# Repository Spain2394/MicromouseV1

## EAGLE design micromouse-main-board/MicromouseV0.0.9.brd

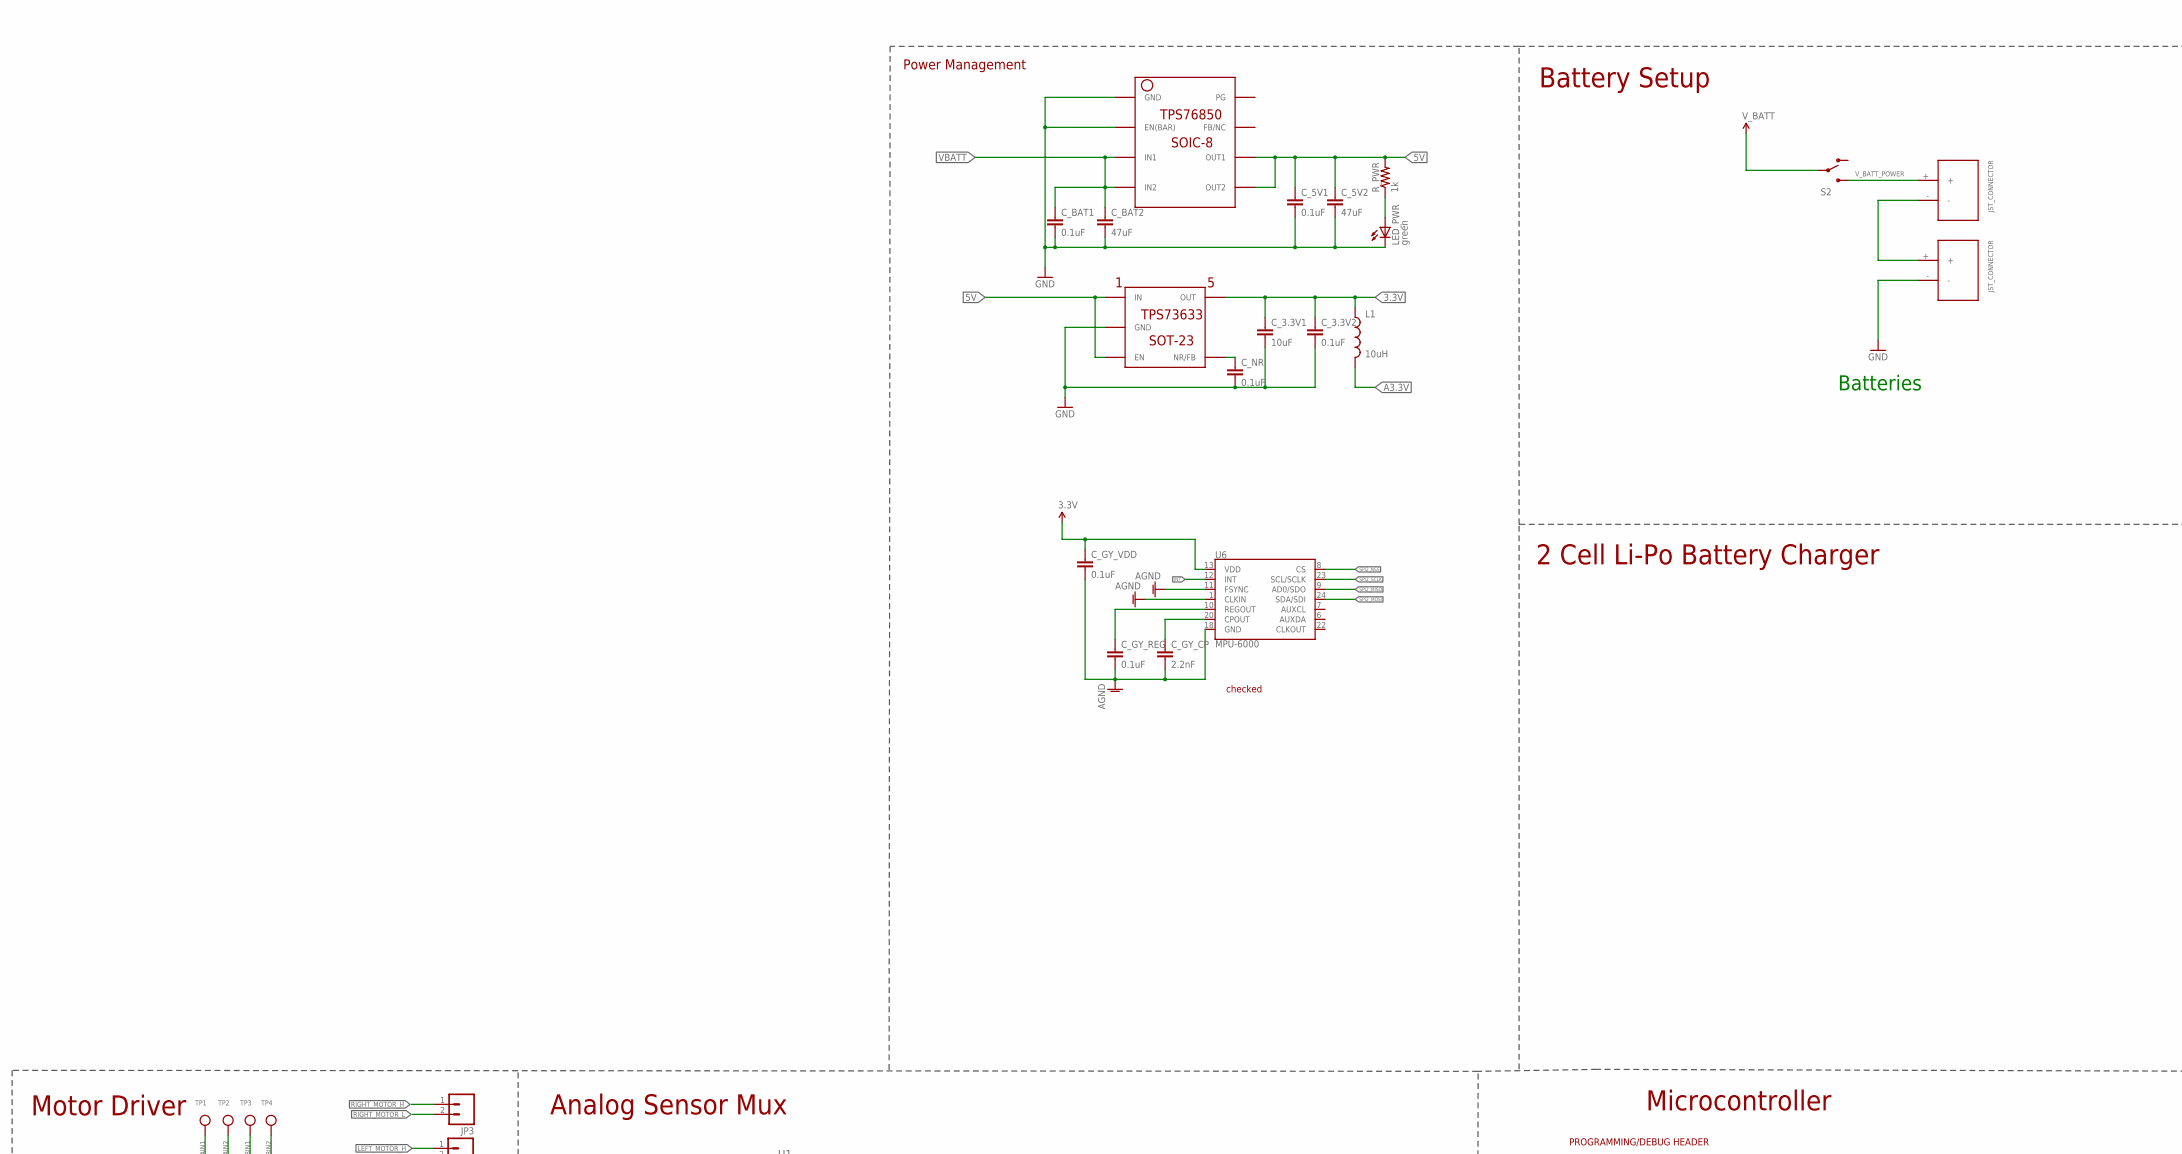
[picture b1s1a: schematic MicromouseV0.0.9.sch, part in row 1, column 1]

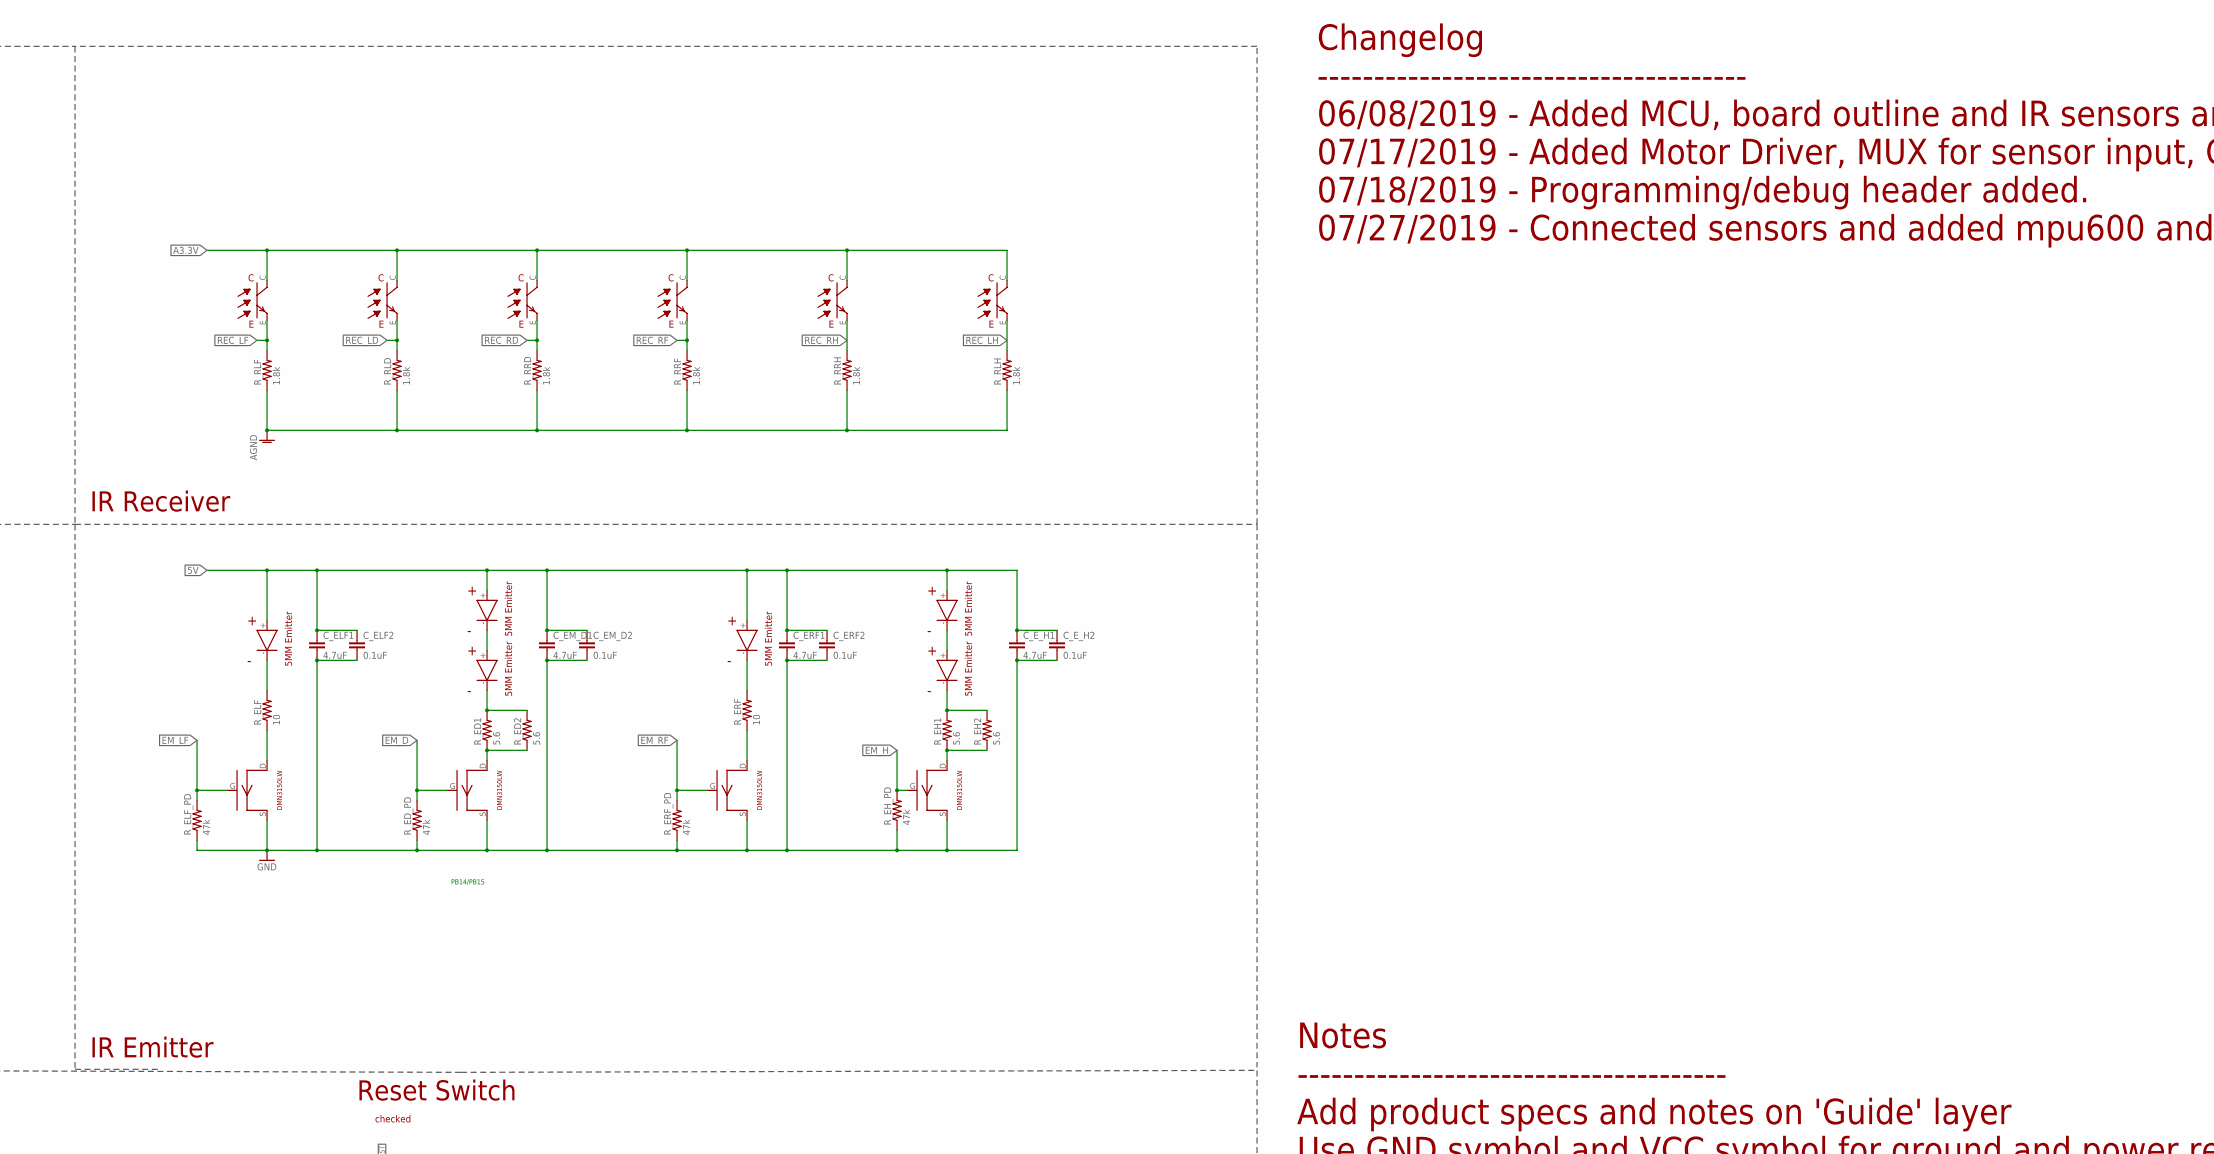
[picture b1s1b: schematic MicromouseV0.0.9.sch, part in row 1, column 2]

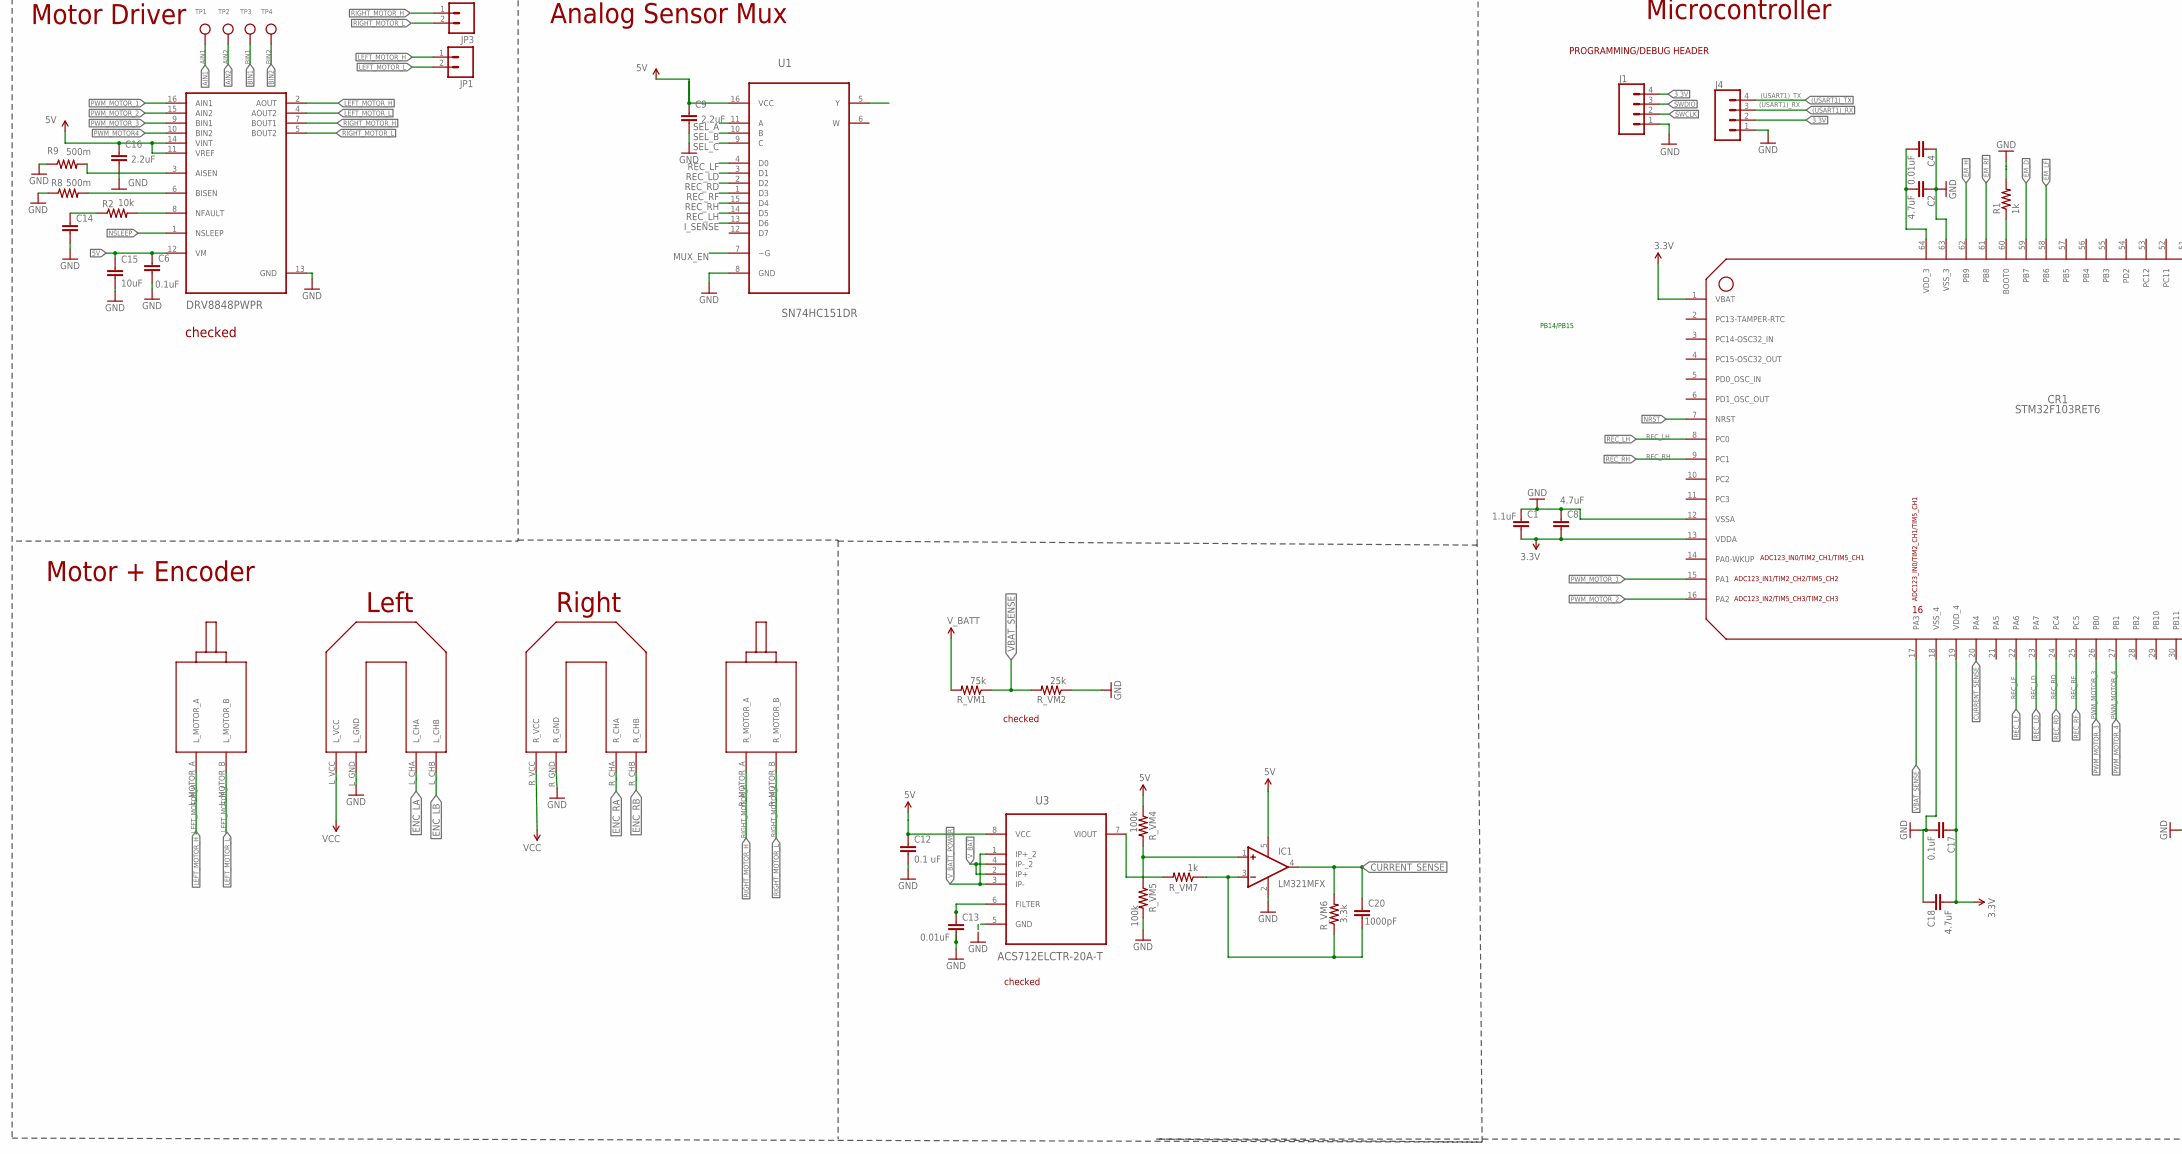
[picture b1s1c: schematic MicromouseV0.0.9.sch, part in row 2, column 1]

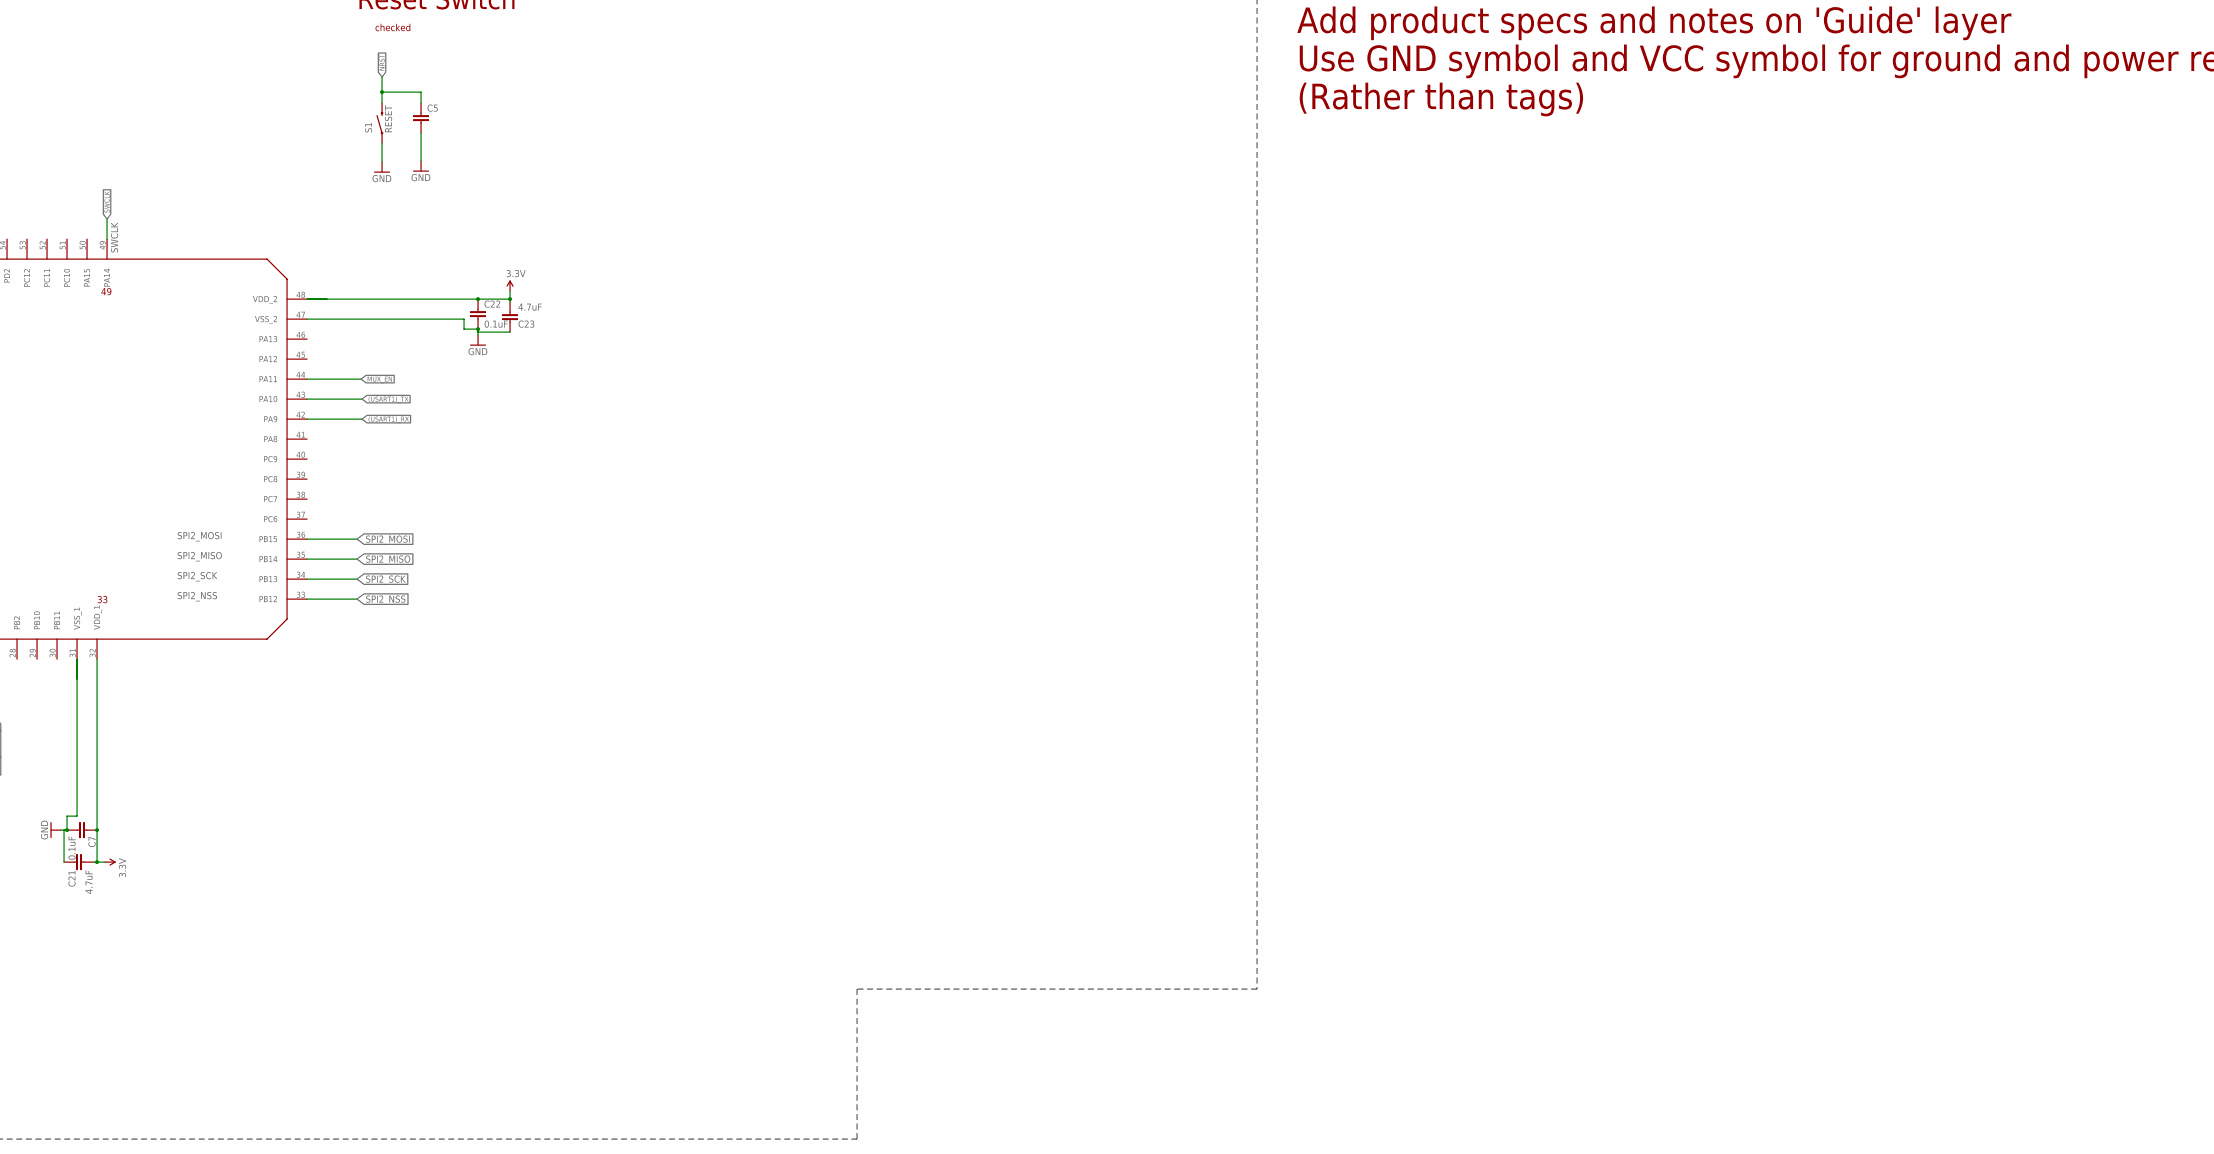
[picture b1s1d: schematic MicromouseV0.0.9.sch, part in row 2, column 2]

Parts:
C1: 1.1uF; 0603-CAP
C2, C8, C18, C21, C23: 4.7uF; 0603-CAP
C4, C13: 0.01uF; 0603-CAP
C5, C14: CAP0603-CAP; 0603-CAP
C6, C7, C17, C22: 0.1uF; 0603-CAP
C9, C16: 2.2uF; 0603-CAP
C12: 0.1 uF; 0603-CAP
C15: 10uF; 0603-CAP
C20: 1000pF; 0603-CAP
CR1: STM32F103RET6; LQFP-64
C_3.3V1: 10uF; 0603-CAP
C_3.3V2, C_5V1: 0.1uF; 0603-CAP
C_5V2: 47uF; 1210
C_BAT1: 0.1uF; 0603-CAP
C_BAT2: 47uF; 1210
C_ELF1: 4.7uF; 0603-CAP
C_ELF2: 0.1uF; 0603-CAP
C_EM_D1: 4.7uF; 0603-CAP
C_EM_D2: 0.1uF; 0603-CAP
C_ERF1: 4.7uF; 0603-CAP
C_ERF2: 0.1uF; 0603-CAP
C_E_H1: 4.7uF; 0603-CAP
C_E_H2: 0.1uF; 0603-CAP
C_GY_CP: 2.2nF; 0603-CAP
C_GY_REG: 0.1uF; 0603-CAP
C_GY_VDD: 0.1uF; 0603-CAP
C_NR: 0.1uF; 0603-CAP
IC1: LM321MFX; SOT23-5
J1, J4: CONN_04; 1X04
JP1, JP3: M02POLAR; MOLEX-1X2
L1: 10uH; 1007
LED_PWR: green; LED-1206
LEFT_FRONT_EMITTER: EMITTER
NMOS1, NMOS2, NMOS3, NMOS4: DMN3150LW
R1: 1k; M0805
R2: 10k; 0805
R8, R9: 500m; 0805
REC_LF: RECEIVER
R_ED1, R_ED2: 5.6; 0603-RES
R_ED_PD: 47k; 0603-RES
R_EH1, R_EH2: 5.6; 0603-RES
R_EH_PD: 47k; 0603-RES
R_ELF: 10; 0603-RES
R_ELF_PD: 47k; 0603-RES
R_ERF: 10; 0603-RES
R_ERF_PD: 47k; 0603-RES
R_PWR: 1k; 0603-RES
R_RLD: 1.8k; 0603-RES
R_RLF: 1.8k; 0603-RES
R_RLH: 1.8k; 0603-RES
R_RRD: 1.8k; 0603-RES
R_RRF: 1.8k; 0603-RES
R_RRH: 1.8k; 0603-RES
R_VM1: 75k; 0603-RES
R_VM2: 25k; 0603-RES
R_VM4, R_VM5: 100k; 0603-RES
R_VM6: 3.3k; 0603-RES
R_VM7: 1k; 0603-RES
S1: RESET; TACTILE_SWITCH_SMD_4.6X2.8MM
S2: SWITCH-SPSTPTH; SWITCH-SPDT
TP1, TP2, TP3, TP4: TESTPOINTROUND2MM; TESTPOINT_ROUND_2MM
U1: SN74HC151DR; SOIC127P600X175-16N
U2: DRV8848PWPR; SOP65P640X120-17N
U3: ACS712ELCTR-20A-T; SOIC127P600X175-8N
U6: MPU-6000; QFN-24-EP
U$1, U$2: JST_CONNECTOR_FEMALE
U$3: TPS73633(SOT-23)
U$4: TPS76850(SOIC-8)
U$7, U$8, U$9, U$20, U$21: RECEIVER
U$11, U$13, U$17, U$18, U$19: EMITTER
U$12: MY_MM_MOTOR_MOUNT

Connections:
3.3V: C7.1, C17.1, C18.2, C21.2, CR1.1 (VBAT), CR1.19 (VDD_4), CR1.32 (VDD_1), C_3.3V1.1, C_3.3V2.1, C_GY_VDD.1, J1.4, J4.2, L1.1, U6.13 (VDD), U$3.OUT
5V: C6.1, C9.1, C15.1, C16.1, C_5V1.1, C_5V2.1, C_ELF1.1, C_ELF2.1, C_EM_D1.1, C_EM_D2.1, C_ERF1.1, C_ERF2.1, C_E_H1.1, C_E_H2.1, LEFT_FRONT_EMITTER.+, R_PWR.2, U1.16 (VCC), U2.11 (VREF), U2.12 (VM), U2.14 (VINT), U$3.EN, U$3.IN, U$4.OUT1, U$4.OUT2, U$11.+, U$13.+, U$18.+
(USART1)_RX: CR1.42 (PA9), J4.3
(USART1)_TX: CR1.43 (PA10), J4.4
A3.3V: L1.2, REC_LF.C, U$7.C, U$8.C, U$9.C, U$20.C, U$21.C
AGND: C_GY_CP.2, C_GY_REG.2, C_GY_VDD.2, R_RLD.1, R_RLF.1, R_RLH.1, R_RRD.1, R_RRF.1, R_RRH.1, U6.1 (CLKIN), U6.11 (FSYNC), U6.18 (GND)
AGROUND: C14.2
AIN1: TP1.P$1
AIN2: TP2.P$1
BIN1: TP3.P$1
BIN2: TP4.P$1
CURRENT_SENSE: C20.1, CR1.20 (PA4), IC1.4 (OUT), R_VM6.2
D2_EM: R_ED1.2, R_ED2.2, U$17.-
D_EM: U$11.-, U$17.+
EM_D: CR1.59 (PB7), NMOS2.G, R_ED_PD.2
EM_H: CR1.62 (PB9), NMOS4.G, R_EH_PD.2
EM_LF: CR1.58 (PB6), NMOS1.G, R_ELF_PD.2
EM_RF: CR1.61 (PB8), NMOS3.G, R_ERF_PD.2
ENC_LA: U$12.L_CHA
ENC_LB: U$12.L_CHB
ENC_RA: U$12.R_CHA
ENC_RB: U$12.R_CHB
GND: C1.1, C2.1, C4.1, C5.2, C6.2, C8.1, C9.2, C12.2, C13.2, C15.2, C16.2, C17.2, C18.1, C22.2, C23.1, CR1.12 (VSSA), CR1.18 (VSS_4), CR1.47 (VSS_2), CR1.63 (VSS_3), C_3.3V1.2, C_3.3V2.2, C_5V1.2, C_5V2.2, C_BAT1.2, C_BAT2.2, C_ELF1.2, C_ELF2.2, C_EM_D1.2, C_EM_D2.2, C_ERF1.2, C_ERF2.2, C_E_H1.2, C_E_H2.2, C_NR.2, IC1.2 (V-), J1.1, J4.1, LED_PWR.C, NMOS1.S, NMOS2.S, NMOS3.S, NMOS4.S, R1.2, R8.1, R9.1, R_ED_PD.1, R_EH_PD.1, R_ELF_PD.1, R_ERF_PD.1, R_VM2.1, R_VM5.2, S1.1, S1.2 (1), U1.8 (GND), U2.13 (GND), U3.5 (GND), U$1.-, U$3.GND, U$4.EN(BAR), U$4.GND, U$12.L_GND, U$12.R_GND
H2_EM: R_EH1.2, R_EH2.2, U$19.-
H_EM: U$18.-, U$19.+
INT: U6.12 (INT)
I_SENSE: U1.13 (D6)
LEFT_MOTOR_H: JP1.1, U2.2 (AOUT), U$12.L_MOTOR_A
LEFT_MOTOR_L: JP1.2, U2.4 (AOUT2), U$12.L_MOTOR_B
LF_EM: LEFT_FRONT_EMITTER.-, R_ELF.2
MUX_EN: CR1.44 (PA11), U1.7 (~G)
unnamed: C13.1, U3.6 (FILTER)
unnamed: C22.1, C23.2, CR1.48 (VDD_2)
unnamed: C7.2, C21.1, CR1.31 (VSS_1)
unnamed: NMOS3.D, R_ERF.1
unnamed: NMOS1.D, R_ELF.1
unnamed: CR1.60 (BOOT0), R1.1
unnamed: U$1.+, U$2.-
unnamed: R2.2, U2.8 (NFAULT)
unnamed: C14.1, R2.1
unnamed: R9.2, U2.3 (AISEN)
unnamed: NMOS2.D, R_ED1.1, R_ED2.1
unnamed: NMOS4.D, R_EH1.1, R_EH2.1
unnamed: R8.2, U2.6 (BISEN)
unnamed: IC1.1 (+IN), R_VM4.2, R_VM5.1
unnamed: R_VM7.2, U3.7 (VIOUT)
unnamed: C2.2, C4.2, CR1.64 (VDD_3)
unnamed: C_NR.1, U$3.NR/FB
unnamed: LED_PWR.A, R_PWR.1
unnamed: C_GY_REG.1, U6.10 (REGOUT)
unnamed: C_GY_CP.1, U6.20 (CPOUT)
unnamed: C20.2, IC1.3 (-IN), R_VM6.1, R_VM7.1
NRST: C5.1, CR1.7 (NRST), S1.3 (2), S1.4 (2)
NSLEEP: U2.1 (NSLEEP)
PWM_MOTOR4: U2.10 (BIN2)
PWM_MOTOR_1: CR1.15 (PA1), U2.16 (AIN1)
PWM_MOTOR_2: CR1.16 (PA2), U2.15 (AIN2)
PWM_MOTOR_3: CR1.26 (PB0), U2.9 (BIN1)
PWM_MOTOR_4: CR1.27 (PB1)
REC_LD: CR1.23 (PA7), R_RLD.2, U1.3 (D1), U$7.E
REC_LF: CR1.22 (PA6), REC_LF.E, R_RLF.2, U1.4 (D0)
REC_LH: CR1.8 (PC0), R_RLH.2, U1.14 (D5), U$21.E
REC_RD: CR1.24 (PC4), R_RRD.2, U1.2 (D2), U$8.E
REC_RF: CR1.25 (PC5), R_RRF.2, U1.1 (D3), U$9.E
REC_RH: CR1.9 (PC1), R_RRH.2, U1.15 (D4), U$20.E
RF_EM: R_ERF.2, U$13.-
RIGHT_MOTOR_H: JP3.1, U2.7 (BOUT1), U$12.R_MOTOR_A
RIGHT_MOTOR_L: JP3.2, U2.5 (BOUT2), U$12.R_MOTOR_B
SEL_A: U1.11 (A)
SEL_B: U1.10 (B)
SEL_C: U1.9 (C)
SPI2_MISO: CR1.35 (PB14), U6.9 (AD0/SDO)
SPI2_MOSI: CR1.36 (PB15), U6.24 (SDA/SDI)
SPI2_NSS: CR1.33 (PB12), U6.8 (CS)
SPI2_SCK: CR1.34 (PB13)
SPI2_SCLK: U6.23 (SCL/SCLK)
SWCLK: CR1.49 (PA14), J1.2
SWDIO: J1.3
VBATT: C_BAT1.1, C_BAT2.1, U$4.IN1, U$4.IN2
VBAT_SENSE: CR1.17 (PA3), R_VM1.1, R_VM2.2
VCC: C1.2, C8.2, CR1.13 (VDDA), U$12.L_VCC, U$12.R_VCC
V_BAT: U3.2 (IP+), U3.4 (IP-_2)
V_BATT: C12.1, IC1.5 (V+), R_VM1.2, R_VM4.1, S2.2, U3.8 (VCC)
V_BATT_POWER: S2.3 (S), U3.1 (IP+_2), U3.3 (IP-), U$2.+

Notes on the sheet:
Changelog -------------------------------------- 06/08/2019 - Added MCU, board outline and IR sensors and receivers. 07/17/2019 - Added Motor Driver, MUX for sensor input, Current Sensor, picked GPIO to use for MUX select, picked ADC in to route MUX to. 07/18/2019 - Programming/debug header added. 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
Notes -------------------------------------- Add product specs and notes on 'Guide' layer Use GND symbol and VCC symbol for ground and power respectively. (Rather than tags)
PROGRAMMING/DEBUG HEADER
Microcontroller
Reset Switch
Motor + Encoder
Motor Driver
IR Emitter
IR Receiver
2 Cell Li-Po Battery Charger
Analog Sensor Mux
Batteries
Battery Setup
ADC123_IN0/TIM2_CH1/TIM5_CH1
ADC123_IN1/TIM2_CH2/TIM5_CH2
ADC123_IN2/TIM5_CH3/TIM2_CH3
checked
PB14/PB15
Power Management

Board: 2 copper layers, 103 parts (0 on the bottom side), 64 nets, no tracks yet.

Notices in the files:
parts and their libraries:
SparkFun-Electromechanical: Licensing: Creative Commons ShareAlike 4.0 International - https://creativecommons.org/licenses/by-sa/4.0
SparkFun: Licensing: CC v3.0 Share-Alike You are welcome to use this library for commercial purposes.
